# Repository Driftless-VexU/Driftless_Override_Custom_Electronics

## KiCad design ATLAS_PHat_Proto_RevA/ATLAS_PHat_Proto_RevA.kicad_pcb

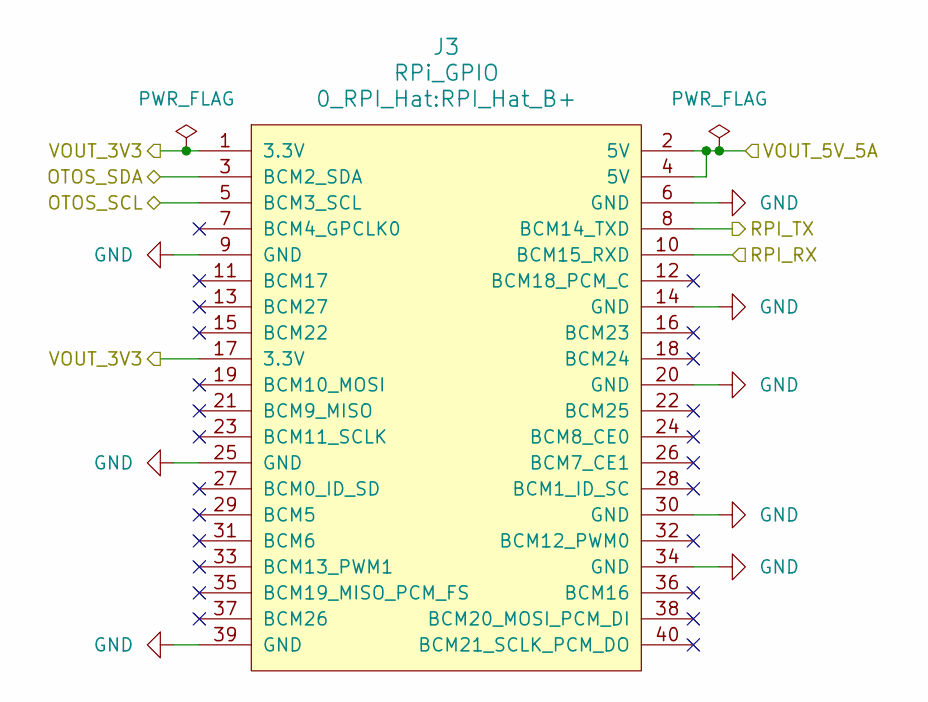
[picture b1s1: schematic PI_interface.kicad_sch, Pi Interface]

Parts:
J3: RPi_GPIO; RPI_Hat_B+

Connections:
/Buck Converter/VOUT_5V_5A: J3.2 (5V), J3.4 (5V); also elsewhere on the board
/Communication Interface/RPI_RX: J3.10 (BCM15_RXD); also elsewhere on the board
/Communication Interface/RPI_TX: J3.8 (BCM14_TXD); also elsewhere on the board
/Communication Interface/VOUT_3V3: J3.1 (3.3V), J3.17 (3.3V); also elsewhere on the board
/OTOS Interface/OTOS_SCL: J3.5 (BCM3_SCL); also elsewhere on the board
/OTOS Interface/OTOS_SDA: J3.3 (BCM2_SDA); also elsewhere on the board
GND: J3.6 (GND), J3.9 (GND), J3.14 (GND), J3.20 (GND), J3.25 (GND), J3.30 (GND), J3.34 (GND), J3.39 (GND); also elsewhere on the board

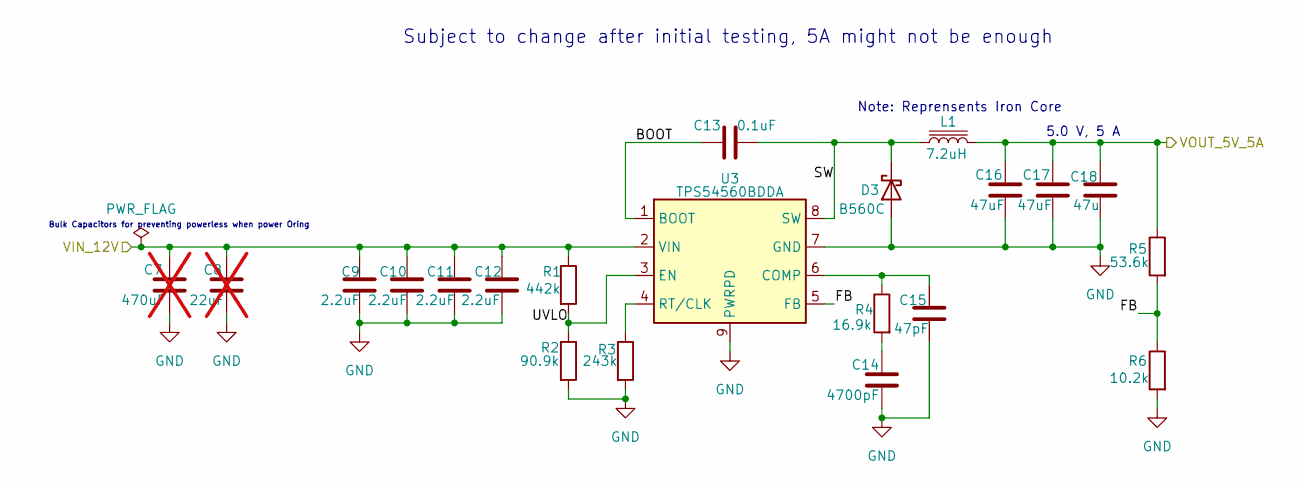
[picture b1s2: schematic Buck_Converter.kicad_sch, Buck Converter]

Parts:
C7: 470uF; C_Radial_D6.3mm_H7.0mm_P2.50mm; not fitted
C8: 22uF; C_1206_3216Metric; not fitted
C9, C10, C11, C12: 2.2uF; C_0603_1608Metric
C13: 0.1uF; C_0603_1608Metric
C14: 4700pF; C_0603_1608Metric
C15: 47pF; C_0603_1608Metric
C16, C17: 47uF; C_0603_1608Metric
C18: 47u; C_0603_1608Metric
D3: B560C; D_SMC
L1: 7.2uH; L_10.4x10.4_H4.8
R1: 442k; R_0603_1608Metric
R2: 90.9k; R_0603_1608Metric
R3: 243k; R_0603_1608Metric
R4: 16.9k; R_0603_1608Metric
R5: 53.6k; R_0603_1608Metric
R6: 10.2k; R_0603_1608Metric
U3: TPS54560BDDA; Texas_R-PDSO-G8_EP2.95x4.9mm_Mask2.4x3.1mm_ThermalVias

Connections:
/Buck Converter/BOOT: C13.1, U3.1 (BOOT)
/Buck Converter/FB: R5.2, R6.1, U3.5 (FB)
/Buck Converter/SW: C13.2, D3.1 (K), L1.1, U3.8 (SW)
/Buck Converter/UVLO: R1.2, R2.1, U3.3 (EN)
/Buck Converter/VIN_12V: C7.1, C8.1, C9.1, C10.1, C11.1, C12.1, R1.1, U3.2 (VIN); also elsewhere on the board
/Buck Converter/VOUT_5V_5A: C16.1, C17.1, C18.1, L1.2, R5.1; also elsewhere on the board
GND: C7.2, C8.2, C9.2, C10.2, C11.2, C12.2, C14.2, C15.2, C16.2, C17.2, C18.2, D3.2 (A), R2.2, R3.2, R6.2, U3.7 (GND), U3.9 (PWRPD); also elsewhere on the board
unnamed: C14.1, R4.2
unnamed: C15.1, R4.1, U3.6 (COMP)
unnamed: R3.1, U3.4 (RT/CLK)

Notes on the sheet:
Subject to change after initial testing, 5A might not be enough
Bulk Capacitors for preventing powerless when power Oring
5.0 V, 5 A
Note: Reprensents Iron Core

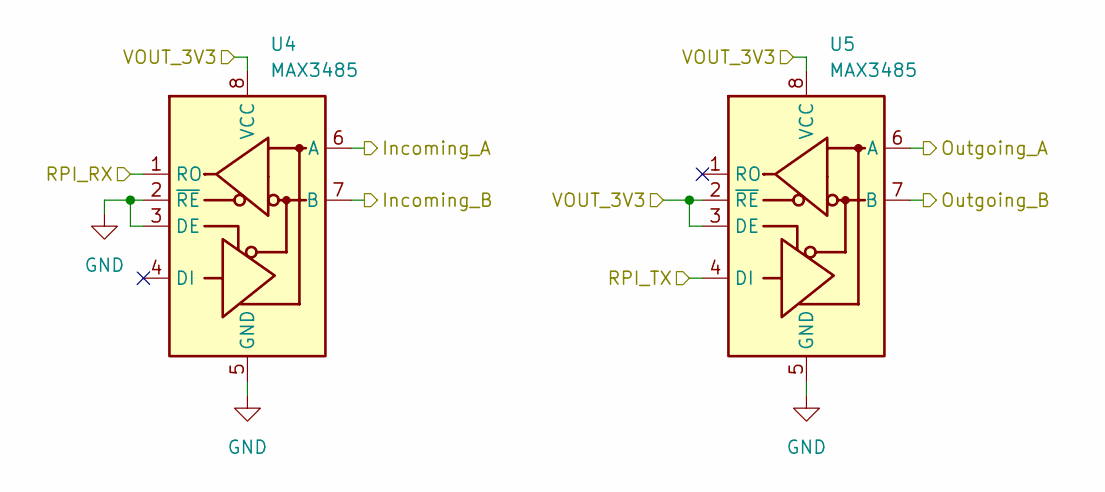
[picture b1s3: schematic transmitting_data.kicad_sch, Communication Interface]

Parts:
U4, U5: MAX3485; SOIC-8_3.9x4.9mm_P1.27mm

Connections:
/Brain Interface/Incoming_A: U4.6 (A); also elsewhere on the board
/Brain Interface/Incoming_B: U4.7 (B); also elsewhere on the board
/Brain Interface/Outgoing_A: U5.6 (A); also elsewhere on the board
/Brain Interface/Outgoing_B: U5.7 (B); also elsewhere on the board
/Communication Interface/RPI_RX: U4.1 (RO); also elsewhere on the board
/Communication Interface/RPI_TX: U5.4 (DI); also elsewhere on the board
/Communication Interface/VOUT_3V3: U4.8 (VCC), U5.2 (~RE), U5.3 (DE), U5.8 (VCC); also elsewhere on the board
GND: U4.2 (~RE), U4.3 (DE), U4.5 (GND), U5.5 (GND); also elsewhere on the board

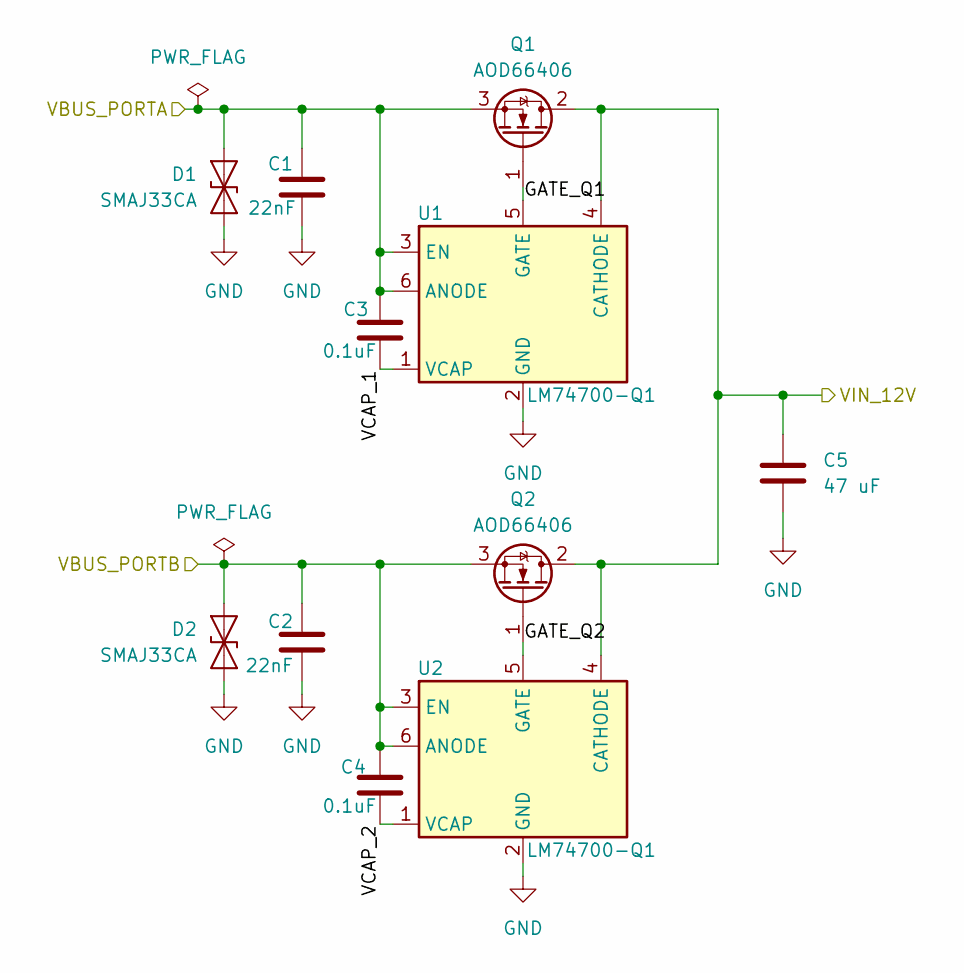
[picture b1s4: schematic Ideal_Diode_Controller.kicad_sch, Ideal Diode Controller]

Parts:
C1, C2: 22nF; C_0603_1608Metric
C3, C4: 0.1uF; C_0603_1608Metric
C5: 47 uF; C_1210_3225Metric
D1, D2: SMAJ33CA; D_SMA
Q1, Q2: AOD66406; TO-252-2
U1, U2: LM74700-Q1; TSOT-23-6

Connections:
/Brain Interface/VBUS_PORTA: C1.1, C3.2, D1.2 (A2), Q1.3 (S), U1.3 (EN), U1.6 (ANODE); also elsewhere on the board
/Brain Interface/VBUS_PORTB: C2.1, C4.2, D2.2 (A2), Q2.3 (S), U2.3 (EN), U2.6 (ANODE); also elsewhere on the board
/Buck Converter/VIN_12V: C5.1, Q1.2 (D), Q2.2 (D), U1.4 (CATHODE), U2.4 (CATHODE); also elsewhere on the board
/Ideal Diode Controller/GATE_Q1: Q1.1 (G), U1.5 (GATE)
/Ideal Diode Controller/GATE_Q2: Q2.1 (G), U2.5 (GATE)
/Ideal Diode Controller/VCAP_1: C3.1, U1.1 (VCAP)
/Ideal Diode Controller/VCAP_2: C4.1, U2.1 (VCAP)
GND: C1.2, C2.2, C5.2, D1.1 (A1), D2.1 (A1), U1.2 (GND), U2.2 (GND); also elsewhere on the board

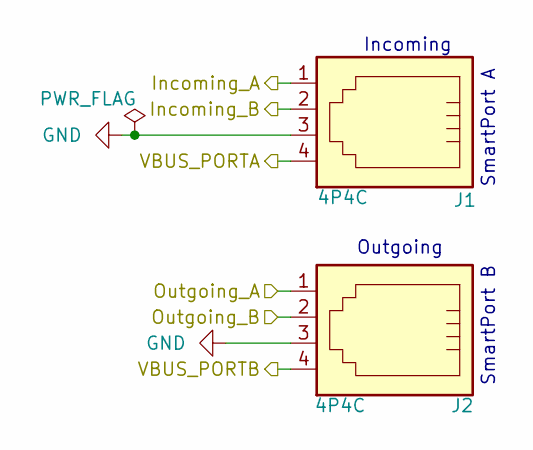
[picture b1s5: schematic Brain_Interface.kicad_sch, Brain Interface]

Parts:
J1, J2: 4P4C; RJ9_Evercom_5301-440xxx_Horizontal

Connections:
/Brain Interface/Incoming_A: J1.1; also elsewhere on the board
/Brain Interface/Incoming_B: J1.2; also elsewhere on the board
/Brain Interface/Outgoing_A: J2.1; also elsewhere on the board
/Brain Interface/Outgoing_B: J2.2; also elsewhere on the board
/Brain Interface/VBUS_PORTA: J1.4; also elsewhere on the board
/Brain Interface/VBUS_PORTB: J2.4; also elsewhere on the board
GND: J1.3, J2.3; also elsewhere on the board

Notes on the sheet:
Outgoing
SmartPort B
Incoming
SmartPort A

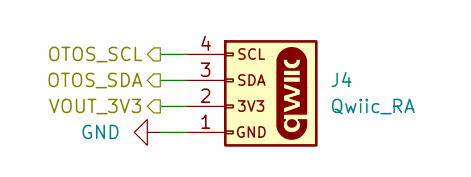
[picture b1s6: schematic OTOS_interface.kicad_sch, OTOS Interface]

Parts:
J4: Qwiic_RA; JST_1x04_P1.0mm_Horizontal_SMD

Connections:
/Communication Interface/VOUT_3V3: J4.2; also elsewhere on the board
/OTOS Interface/OTOS_SCL: J4.4; also elsewhere on the board
/OTOS Interface/OTOS_SDA: J4.3; also elsewhere on the board
GND: J4.1; also elsewhere on the board

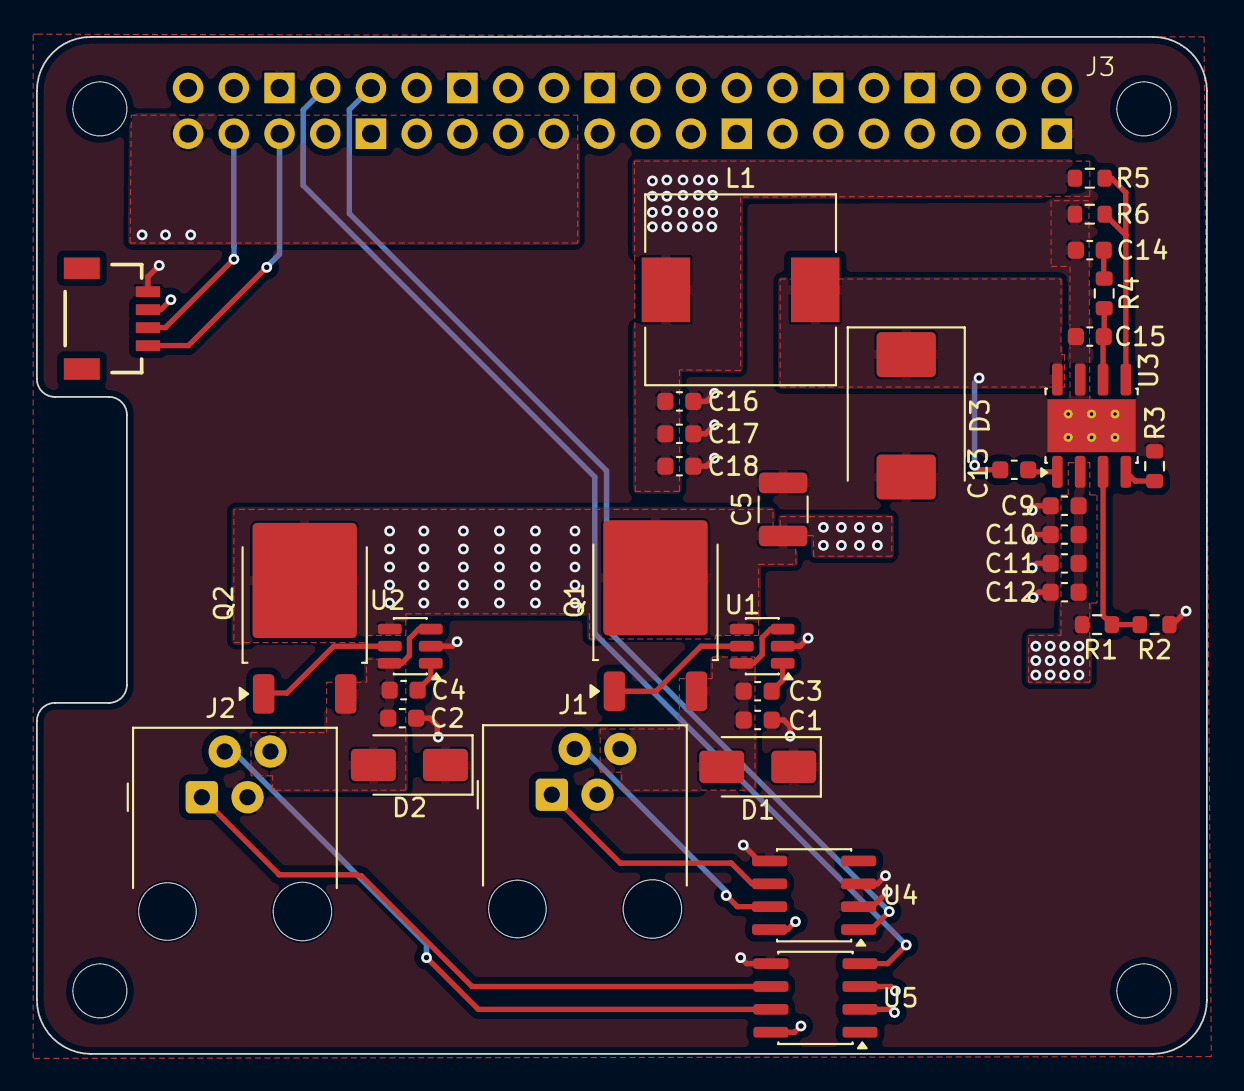
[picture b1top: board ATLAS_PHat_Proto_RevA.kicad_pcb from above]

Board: 4 copper layers, 65.0 x 56.5 mm, 36 parts (0 on the bottom side), 25 nets.

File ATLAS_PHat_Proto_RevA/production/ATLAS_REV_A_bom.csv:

Designator,Footprint,Quantity,Value,LCSC Part #
"C1, C2",0603,2,22nF,
"C10, C11, C12, C9",0603,4,2.2uF,
"C13, C3, C4",0603,3,0.1uF,
C14,0603,1,4700pF,
C15,0603,1,47pF,
"C16, C17",0603,2,47uF,
C18,0603,1,47u,
C5,1210,1,47 uF,
"D1, D2",D_SMA,2,SMAJ33CA,
D3,D_SMC,1,B560C,
"J1, J2",RJ9_Evercom_5301-440xxx_Horizontal,2,4P4C,
J3,RPI_Hat_B+,1,RPi_GPIO,
J4,JST_1x04_P1.0mm_Horizontal_SMD,1,Qwiic_RA,
L1,L_10.4x10.4_H4.8,1,7.2uH,
"Q1, Q2",TO-252-2,2,AOD66406,
R1,0603,1,442k,
R2,0603,1,90.9k,
R3,0603,1,243k,
R4,0603,1,16.9k,
R5,0603,1,53.6k,
R6,0603,1,10.2k,
"U1, U2",TSOT-23-6,2,LM74700-Q1,
U3,Texas_R-PDSO-G8_EP2.95x4.9mm_Mask2.4x3.1mm_ThermalVias,1,TPS54560BDDA,
"U4, U5",SOIC-8_3.9x4.9mm_P1.27mm,2,MAX3485,
